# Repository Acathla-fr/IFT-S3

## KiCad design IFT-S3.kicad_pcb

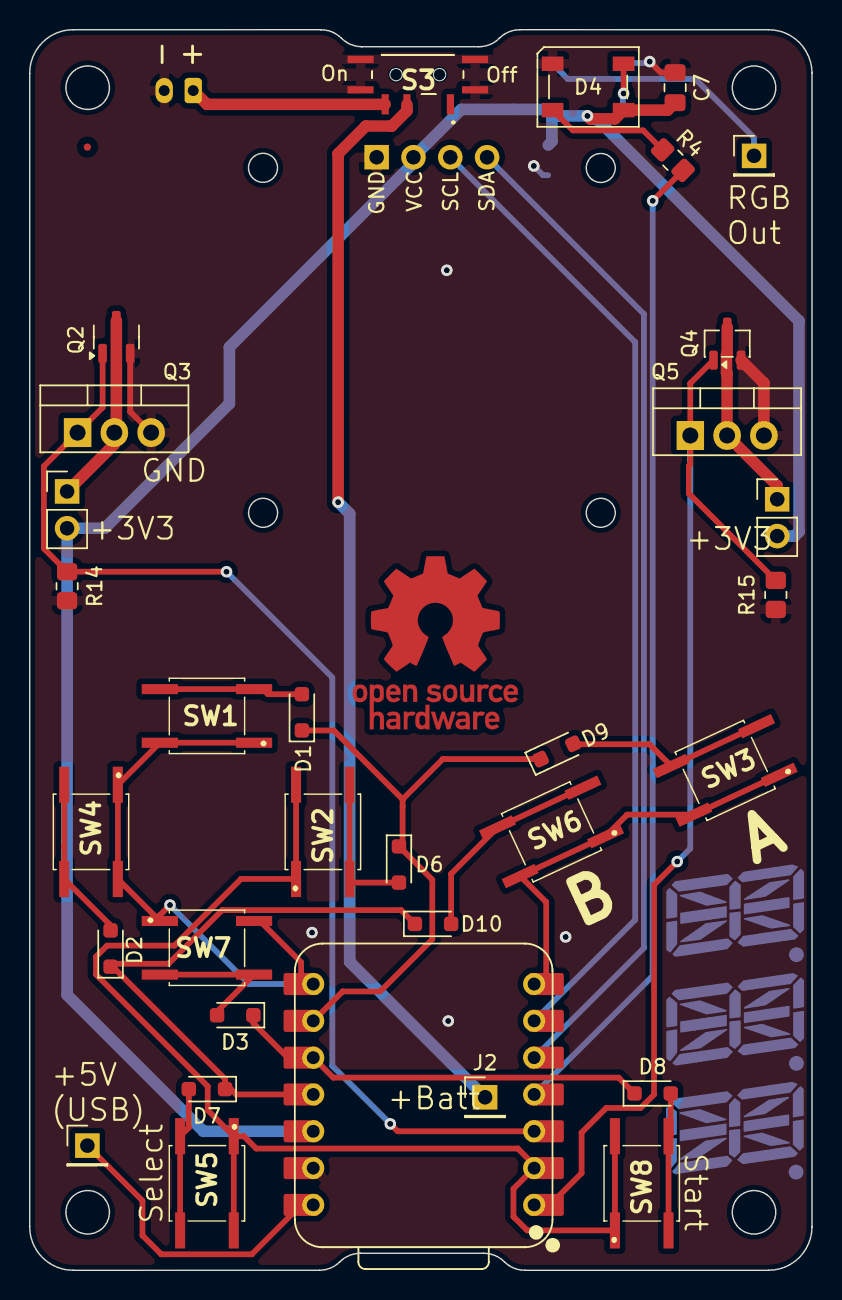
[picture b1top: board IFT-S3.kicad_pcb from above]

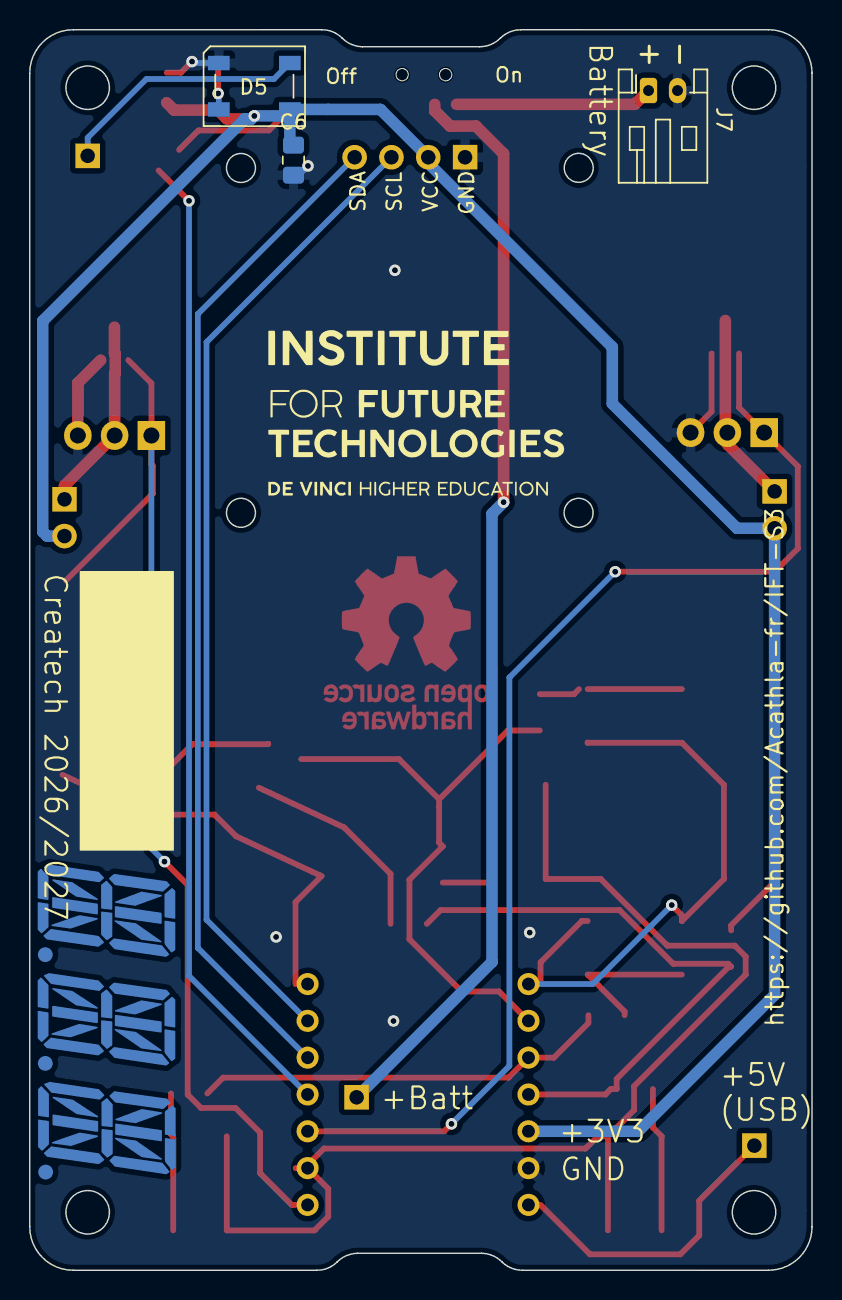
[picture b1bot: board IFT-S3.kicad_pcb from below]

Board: 2 copper layers, 54.0 x 85.6 mm, 36 parts (3 on the bottom side), 29 nets.

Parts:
C6, C7: 10u; C_0805_2012Metric_Pad1.18x1.45mm_HandSolder
D1, D2, D3, D6, D7, D8, D9, D10: 1N4148WS; D_SOD-323_HandSoldering
D4, D5: Inolux_IN-PI554FCH; LED_Inolux_IN-PI554FCH_PLCC4_5.0x5.0mm_P3.2mm
J1: Conn_01x04_Socket; SSD1306_module
J2, J5, J6: Conn_01x01_Pin; PinHeader_1x01_P2.54mm_Vertical
J3, J4: Conn_01x02_Pin; PinHeader_1x02_P2.54mm_Vertical
J7: Conn_01x02; JST_PH_S2B-PH-K_1x02_P2.00mm_Horizontal
Q2, Q4: Q_NMOS_GSD; SOT-23-3
Q3, Q5: IRLZ44N; TO-220-3_Vertical
R4: 330; R_0805_2012Metric_Pad1.20x1.40mm_HandSolder
R14, R15: 10K; R_0805_2012Metric_Pad1.20x1.40mm_HandSolder
S3: MSK12C02
SW1, SW2, SW3, SW4, SW5, SW6, SW7, SW8: PTS526_SK15_SMTR2_LFS; PTS526SK15SMTR2LFS
U1: XIAO-ESP32-S3-DIP; XIAO-ESP32S3-DIP

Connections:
+3.3V: C6.1, C7.1, D4.3 (VDD), D5.3 (VDD), J1.2, J3.2, J4.2, U1.12 (VCC_3V3)
+BATT: J7.1, S3.C1 (NO)
+BATT_after_switch: J2.1 (Pin_1_1), S3.B1 (COM)
/RGB_OUT: D5.4 (DO), J5.1 (Pin_1_1)
/SCL: J1.3, U1.6 (GPIO9/D5/I2C_SCL)
/SDA: J1.4, U1.5 (GPIO5/D4/I2C_SDA)
/drain: J4.1, Q4.3 (D), Q5.2 (D)
/drain2: J3.1, Q2.3 (D), Q3.2 (D)
GND: C6.2, C7.2, D4.1 (VSS), D5.1 (VSS), J1.1, J7.2, Q2.2 (S), Q3.3 (S), Q4.2 (S), Q5.3 (S), R14.2, R15.2, S3.MP1, S3.MP2, S3.MP3, S3.MP4, U1.13 (GND)
I_1: D1.1 (K), D6.1 (K), D9.1 (K), U1.9 (GPIO7/D8/A8/SCK)
I_2: D2.1 (K), D7.1 (K), D10.1 (K), U1.11 (GPIO9/D10/A10/MOSI)
I_3: D3.1 (K), D8.1 (K), U1.10 (GPIO8/D9/A9/MISO)
unnamed: D1.2 (A), SW1.2
unnamed: D2.2 (A), SW4.2
unnamed: D3.2 (A), SW7.2
unnamed: D4.2 (DIN), R4.1
unnamed: D4.4 (DO), D5.2 (DIN)
unnamed: D6.2 (A), SW2.2
unnamed: D7.2 (A), SW5.2
unnamed: D8.2 (A), SW8.2
unnamed: D9.2 (A), SW3.2
unnamed: D10.2 (A), SW6.2
unnamed: J6.1 (Pin_1_1), U1.14 (VBUS)
O_1: SW1.1, SW4.1, SW7.1, U1.8 (U0RXD/D7/RX)
O_2: SW2.1, SW5.1, SW8.1, U1.2 (GPIO2/DA/A1)
O_3: SW3.1, SW6.1, U1.7 (U0TXD/D6/TX)
RGB_LEDs: R4.2, U1.4 (GPIO4/D3/A3)
Tr_GATE: Q4.1 (G), Q5.1 (G), R15.1, U1.1 (GPIO1/D0/A0)
Tr_GATE2: Q2.1 (G), Q3.1 (G), R14.1, U1.3 (GPIO3/D2/A2)

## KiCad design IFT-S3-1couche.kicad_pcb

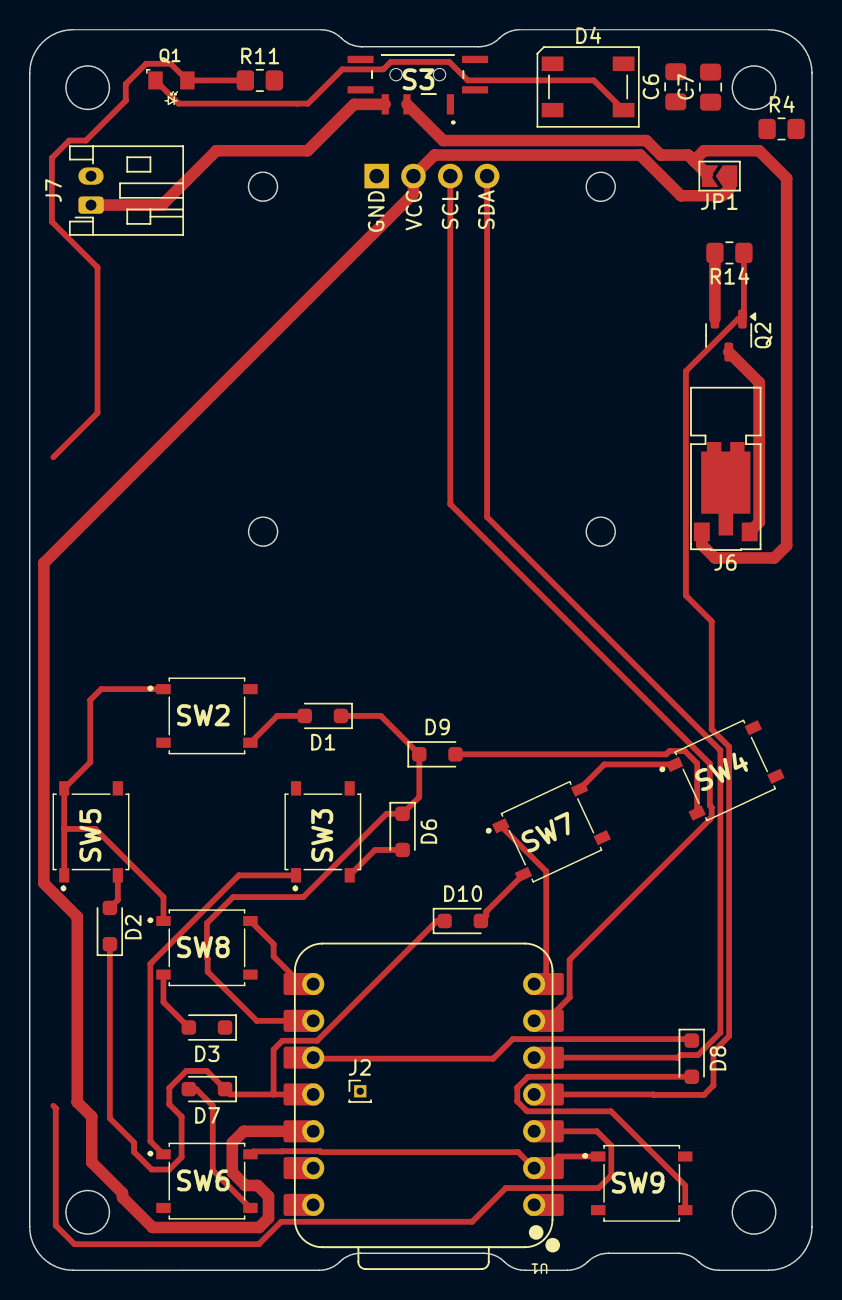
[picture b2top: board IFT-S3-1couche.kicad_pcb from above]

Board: 2 copper layers, 54.0 x 85.6 mm, 32 parts (1 on the bottom side), 26 nets.

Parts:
C6, C7: 10u; C_0805_2012Metric_Pad1.18x1.45mm_HandSolder
D1, D2, D3, D6, D7, D8, D9, D10: 1N4148WS; D_SOD-323_HandSoldering
D4, D5: Inolux_IN-PI554FCH; LED_Inolux_IN-PI554FCH_PLCC4_5.0x5.0mm_P3.2mm
J1: Conn_01x04_Socket; SSD1306_module
J2: Conn_01x01_Pin; PinHeader_1x01_P1.00mm_Vertical
J6: Conn_01x02_Pin; Vybronics_VZ30C1T8219732L
J7: Conn_01x02; JST_PH_S2B-PH-K_1x02_P2.00mm_Horizontal
JP1: SolderJumper_2_Open; SolderJumper-2_P1.3mm_Open_TrianglePad1.0x1.5mm
Q1: Q_Photo_NPN; SFH3710
Q2: Q_NMOS_GSD; SOT-23-3
R4: 330; R_0805_2012Metric_Pad1.20x1.40mm_HandSolder
R11: 1M; R_0805_2012Metric_Pad1.20x1.40mm_HandSolder
R14: 10K; R_0805_2012Metric_Pad1.20x1.40mm_HandSolder
S3: MSK12C02
SW2, SW3, SW4, SW5, SW6, SW7, SW8, SW9: PTS526_SK15_SMTR2_LFS; PTS526SK15SMTR2LFS
U1: XIAO-ESP32-S3-DIP; XIAO-ESP32S3-DIP

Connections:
+3.3V: C6.1, C7.1, D4.3 (VDD), D5.3 (VDD), J1.2, JP1.1 (A), Q1.1 (C), U1.12 (VCC_3V3)
+BATT: J7.1, S3.C1 (NO)
+BATT_after_switch: J2.1, J6.2, JP1.2 (B), S3.B1 (COM)
/SCL: J1.3, U1.6 (GPIO9/D5/I2C_SCL)
/SDA: J1.4, U1.5 (GPIO5/D4/I2C_SDA)
GND: C6.2, C7.2, D4.1 (VSS), D5.1 (VSS), J1.1, J7.2, Q2.2 (S), R11.2, R14.2, S3.MP1, S3.MP2, S3.MP3, S3.MP4, U1.13 (GND)
I_1: D1.1 (K), D6.1 (K), D9.1 (K), U1.9 (GPIO7/D8/A8/SCK)
I_2: D2.1 (K), D7.1 (K), D10.1 (K), U1.11 (GPIO9/D10/A10/MOSI)
I_3: D3.1 (K), D8.1 (K), U1.10 (GPIO8/D9/A9/MISO)
unnamed: D1.2 (A), SW2.3, SW2.4
unnamed: D2.2 (A), SW5.3, SW5.4
unnamed: D3.2 (A), SW8.3, SW8.4
unnamed: D4.2 (DIN), R4.1
unnamed: D4.4 (DO), D5.2 (DIN)
unnamed: D6.2 (A), SW3.3, SW3.4
unnamed: D7.2 (A), SW6.3, SW6.4
unnamed: D8.2 (A), SW9.3, SW9.4
unnamed: D9.2 (A), SW4.3, SW4.4
unnamed: D10.2 (A), SW7.3, SW7.4
O_1: SW2.1, SW2.2, SW5.1, SW5.2, SW8.1, SW8.2, U1.8 (U0RXD/D7/RX)
O_2: SW3.1, SW3.2, SW6.1, SW6.2, SW9.1, SW9.2, U1.2 (GPIO2/DA/A1)
O_3: SW4.1, SW4.2, SW7.1, SW7.2, U1.7 (U0TXD/D6/TX)
Photo_Tr: Q1.2 (E), R11.1, U1.3 (GPIO3/D2/A2)
RGB_LEDs: R4.2, U1.1 (GPIO1/D0/A0)
Tr_DRAIN: J6.1, Q2.3 (D)
Tr_GATE: Q2.1 (G), R14.1, U1.4 (GPIO4/D3/A3)

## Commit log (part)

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2025-09-03 First batch of 30 PCBs sent to fab
2025-09-04 Clean up and OLED 3D model added
